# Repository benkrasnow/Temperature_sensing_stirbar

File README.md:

# Temperature_sensing_stirbar
Schematics, PCB layout, and firmware for an RFID temperature sensor
https://youtu.be/nh1SIfipQs4

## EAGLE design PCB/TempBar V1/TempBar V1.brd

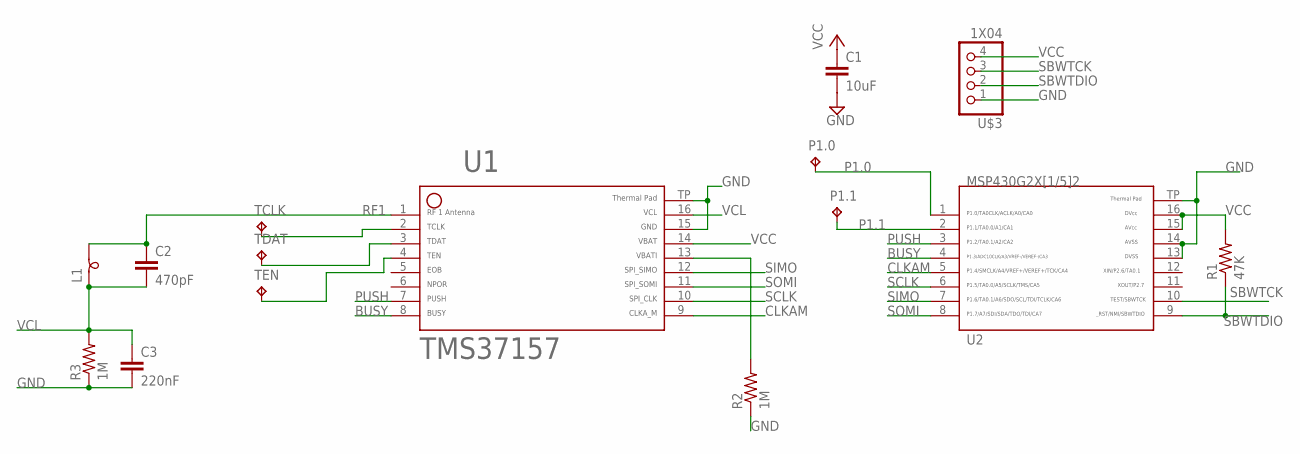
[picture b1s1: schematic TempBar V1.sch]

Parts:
C1: 10uF; C0603
C2: 470pF; C0402
C3: 220nF; C0402
L1: SM-B5
P1.0, P1.1: TPTP08R; TP08R
R1: 47K; R0402
R2, R3: 1M; R0402
TCLK: TPTP08R; TP08R
TDAT: TPTP08R; TP08R
TEN: TPTP08R; TP08R
U1: TMS37157; RSA16
U2: G2X[1/5]2---RSA16; RSA16
U$3: 1X04; 1X06

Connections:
BUSY: U1.8, U2.4
CLKAM: U1.9, U2.5
GND: C1.2, C3.2, R2.1, R3.1, U1.15, U1.TP (PP), U2.13, U2.14, U2.TP, U$3.1
unnamed: R2.2, U1.13
unnamed: TCLK.TP, U1.2
unnamed: TDAT.TP, U1.3
unnamed: TEN.TP, U1.4
P1.0: P1.0.TP, U2.1
P1.1: P1.1.TP, U2.2
PUSH: U1.7, U2.3
RF1: C2.1, L1.2, U1.1
SBWTCK: U2.10, U$3.3
SBWTDIO: R1.1, U2.9, U$3.2
SCLK: U1.10, U2.6
SIMO: U1.12, U2.7
SOMI: U1.11, U2.8
VCC: C1.1, R1.2, U1.14, U2.15, U2.16, U$3.4
VCL: C2.2, C3.1, L1.1, R3.2, U1.16

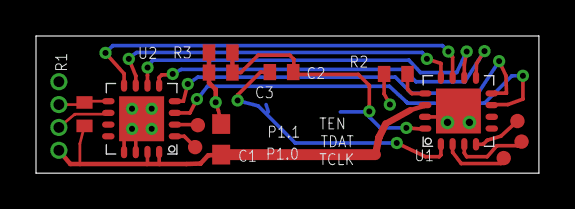
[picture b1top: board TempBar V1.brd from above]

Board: 2 copper layers, 27.9 x 7.6 mm, 15 parts (1 on the bottom side), 18 nets.

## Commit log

2023-04-10 Ran all files through astyle to fix all the weird formatting
